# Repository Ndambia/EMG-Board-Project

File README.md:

# 3-Channel EMG Data Acquisition System (ESP32-Based)

## Overview

This project is a **3-channel Electromyography (EMG) Data Acquisition (DAQ) system** built around an **ESP32 MCU**. It is designed to acquire low-level biopotential signals from muscles, condition them using an analog front-end, digitize them via an external ADC, and transmit or store the data for further processing.

The system is modular and portable, integrating power management for battery operation, making it suitable for wearable and embedded biomedical applications.

---

## Key Features

* Three independent EMG input channels
* External multi-channel ADC with I²C interface
* ESP32 MCU for control, DSP, and communication
* Li-Po battery charging support
* Boost / regulation circuitry for stable operation
* Compact PCB designed for embedded and wearable use

---

## System Architecture

### Signal Chain Overview

```
Muscle Electrodes
      ↓
EMG Analog Front-End (DAQ)
      ↓
External ADC (3 Channels)
      ↓  I²C
ESP32 MCU
      ↓
USB / BLE / Wi-Fi 
```

---

## Functional Block Description

### 1. EMG DAQ (Analog Front-End)

* Three independent EMG channels
* Powered at **3.3 V**
* Outputs conditioned analog signals suitable for ADC input

**Typical functionality includes:**

* Instrumentation amplification
* High-pass filtering to remove motion artifacts
* Low-pass filtering to reduce high-frequency noise
* Optional 50/60 Hz notch filtering

---

### 2. Analog-to-Digital Converter (ADC)

* Powered at **3.3 V**
* Three analog input channels
* Digital interface: **I²C (SDA, SCL)**

The ADC digitizes the conditioned EMG signals for processing by the ESP32.

---

### 3. Microcontroller Unit (ESP32)

* Powered at **3.3 V**
* Configures and reads data from the ADC
* Performs optional digital signal processing (RMS, envelope extraction)
* Supports USB, BLE, and Wi-Fi communication

---

### 4. Power Management

#### Li-Po Battery Charger

* Supports single-cell Li-Po batteries
* USB-powered charging
* Enables portable operation

#### Boost / Regulation Circuit

* Maintains stable system voltage during battery discharge
* Ensures reliable operation of analog and digital blocks

---

## PCB Design

### PCB Back Layer

The back layer shows the ground plane distribution and return paths. Care was taken to maintain a low-impedance ground for the analog EMG front-end to minimize noise coupling from digital sections.

### PCB Front Layer

The front layer contains the majority of signal routing and component placement. Analog EMG paths are kept short and isolated from high-speed digital and power traces.

### PCB Routing Overview

This image provides an overall routing overview, highlighting trace organization, separation between analog and digital domains, and controlled routing for sensitive EMG signals.

### Routing – Front

The front routing layer illustrates how EMG signal traces are carefully routed with minimal vias to reduce interference and preserve signal integrity.

### Routing – Back

Back-side routing is primarily used for ground returns and power distribution, helping to maintain clean reference planes for low-noise acquisition.

### PCB 3D View

The 3D view shows overall board dimensions, component height clearance, and suitability for enclosure or wearable integration.

### PCB Front 3D View

This view highlights top-side component placement, including the ESP32 module, ADC, and EMG front-end circuitry.

### PCB Back 3D View

The back-side 3D view shows passive components, ground stitching vias, and mechanical layout considerations.

### Design Progress Snapshot

This image documents the PCB design progress during layout and routing stages.

### Schematics

The schematic captures the complete system design, including EMG analog front-end, ADC, ESP32 MCU, and power management circuitry.

---

## Intended Applications

* Multi-channel EMG signal acquisition
* Wearable biomedical research devices
* Prosthetics and rehabilitation research
* Gesture recognition and HMI systems
* Academic and laboratory EMG experimentation

---

## Design Notes & Safety

* Proper analog grounding and shielding are critical for low-noise EMG acquisition
* Use shielded electrode cables where possible
* This system is intended for **research and educational use only**
* Not certified for clinical or diagnostic applications

---

## Author

**Eng. Ndambia M.**
MyGen Solutions

---

## License & Disclaimer

This project is provided for **research and educational purposes only**. It is not a certified medical device and must not be used for clinical diagnosis or treatment.

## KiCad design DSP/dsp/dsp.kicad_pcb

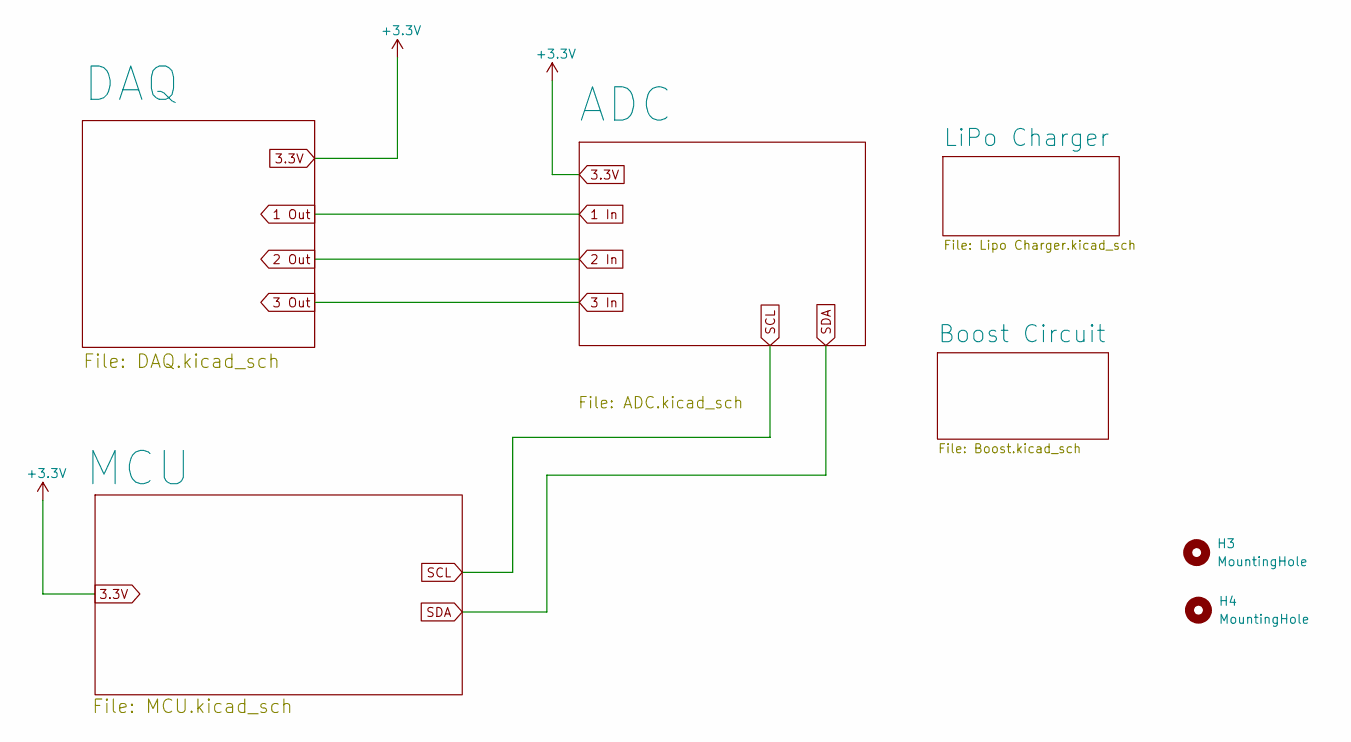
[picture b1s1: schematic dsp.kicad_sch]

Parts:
H3, H4: MountingHole; MountingHole_2.7mm_M2.5_Pad_Via

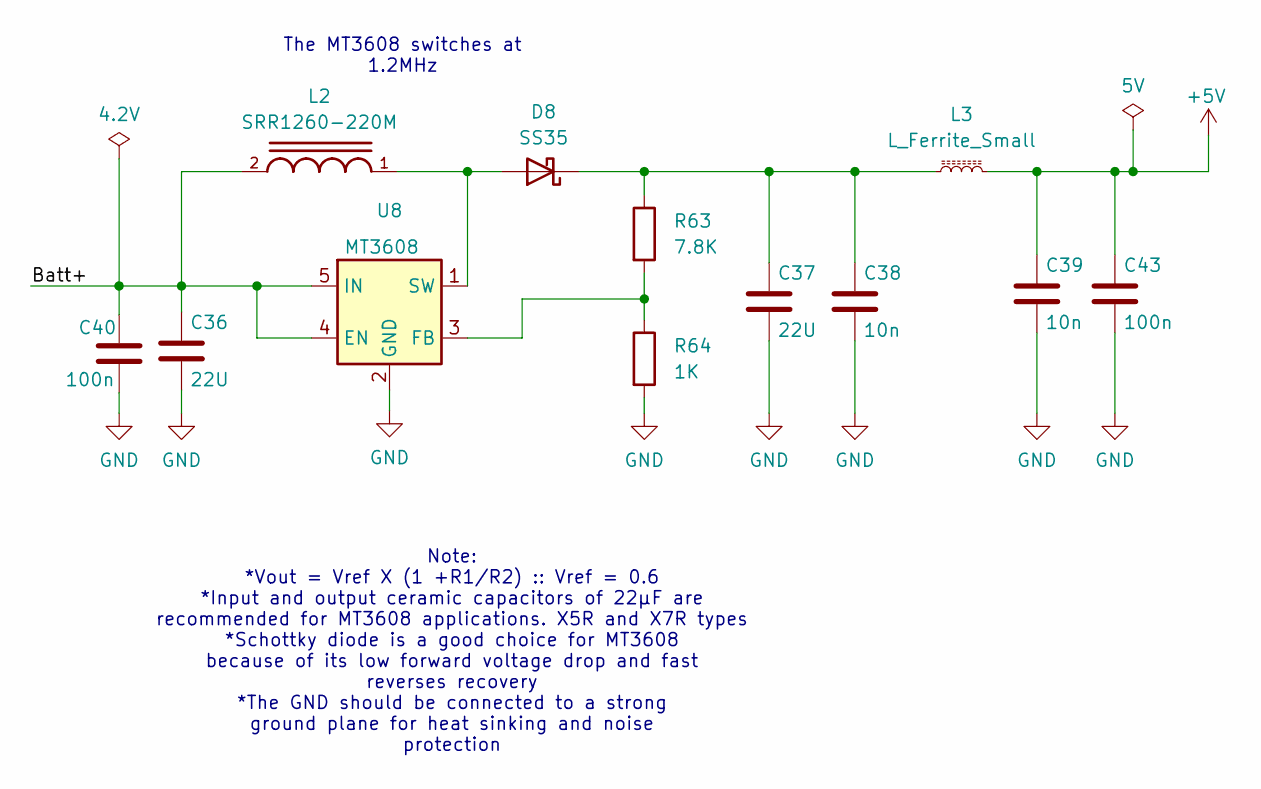
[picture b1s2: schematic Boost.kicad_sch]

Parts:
C36, C37: 22U; C_0201_0603Metric
C38, C39: 10n; C_0201_0603Metric
C40, C43: 100n; C_0201_0603Metric
D8: SS35; D_SMA
L2: SRR1260-220M; INDP125125X600N
L3: L_Ferrite_Small; L_0603_1608Metric
R63: 7.8K; R_0603_1608Metric
R64: 1K; R_0603_1608Metric
U8: MT3608; SOT-23-6

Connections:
5V: C39.1, C43.1, L3.2; also elsewhere on the board
/Boost Circuit/Batt+: C36.1, C40.1, L2.2, U8.4 (EN), U8.5 (IN)
GND: C36.2, C37.2, C38.2, C39.2, C40.2, C43.2, R64.2, U8.2 (GND); also elsewhere on the board
unnamed: D8.2 (A), L2.1, U8.1 (SW)
unnamed: C37.1, C38.1, D8.1 (K), L3.1, R63.1
unnamed: R63.2, R64.1, U8.3 (FB)

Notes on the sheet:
Note: *Vout = Vref X (1 +R1/R2) :: Vref = 0.6 *Input and output ceramic capacitors of 22μF are recommended for MT3608 applications. X5R and X7R types *Schottky diode is a good choice for MT3608 because of its low forward voltage drop and fast reverses recovery *The GND should be connected to a stro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
The MT3608 switches at 1.2MHz

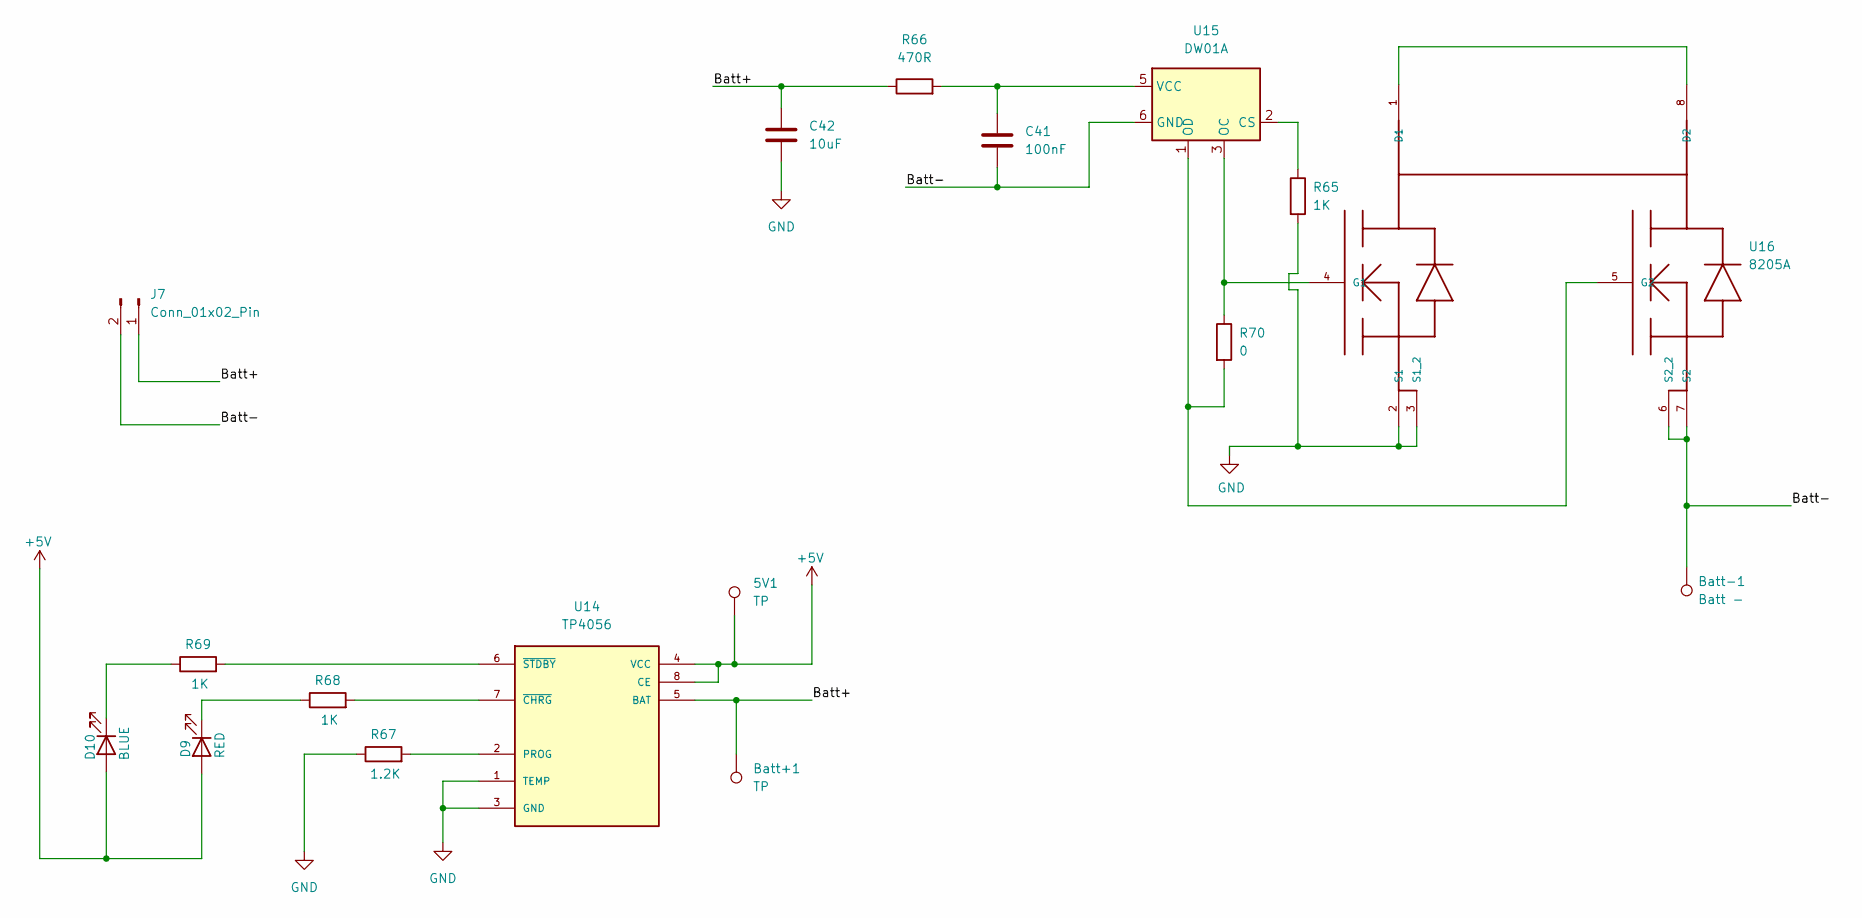
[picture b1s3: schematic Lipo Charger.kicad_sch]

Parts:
5V1: TP; TestPoint_Pad_D1.5mm
Batt+1: TP; TestPoint_Pad_D1.5mm
Batt-1: Batt -; TestPoint_Pad_D1.5mm
C41: 100nF; C_0201_0603Metric
C42: 10uF; C_0201_0603Metric
D9: RED; LED_0402_1005Metric
D10: BLUE; LED_0402_1005Metric
J7: Conn_01x02_Pin; JWT_A3963_1x02_P3.96mm_Vertical
R65, R68, R69: 1K; R_0603_1608Metric
R66: 470R; R_0603_1608Metric
R67: 1.2K; R_0603_1608Metric
R70: 0; R_0603_1608Metric
U14: TP4056; SOP127P600X175-9N
U15: DW01A; SOT-23-6
U16: 8205A; TSSOP8

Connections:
5V: 5V1.1, D9.2 (A), D10.2 (A), U14.4 (VCC), U14.8 (CE); also elsewhere on the board
/LiPo Charger/Batt+: Batt+1.1, C42.1, J7.1, R66.1, U14.5 (BAT)
/LiPo Charger/Batt-: Batt-1.1, C41.2, J7.2, U15.6 (GND), U16.6 (S2_2), U16.7 (S2)
GND: C42.2, R65.2, R67.1, U14.1 (TEMP), U14.3 (GND), U16.2 (S1), U16.3 (S1_2); also elsewhere on the board
unnamed: D9.1 (K), R68.1
unnamed: D10.1 (K), R69.1
unnamed: R67.2, U14.2 (PROG)
unnamed: R68.2, U14.7 (~CHRG)
unnamed: R69.2, U14.6 (~STDBY)
unnamed: R65.1, U15.2 (CS)
unnamed: R70.1, U15.3 (OC), U16.4 (G1)
unnamed: R70.2, U15.1 (OD), U16.5 (G2)
unnamed: C41.1, R66.2, U15.5 (VCC)
unnamed: U16.1 (D1), U16.8 (D2)

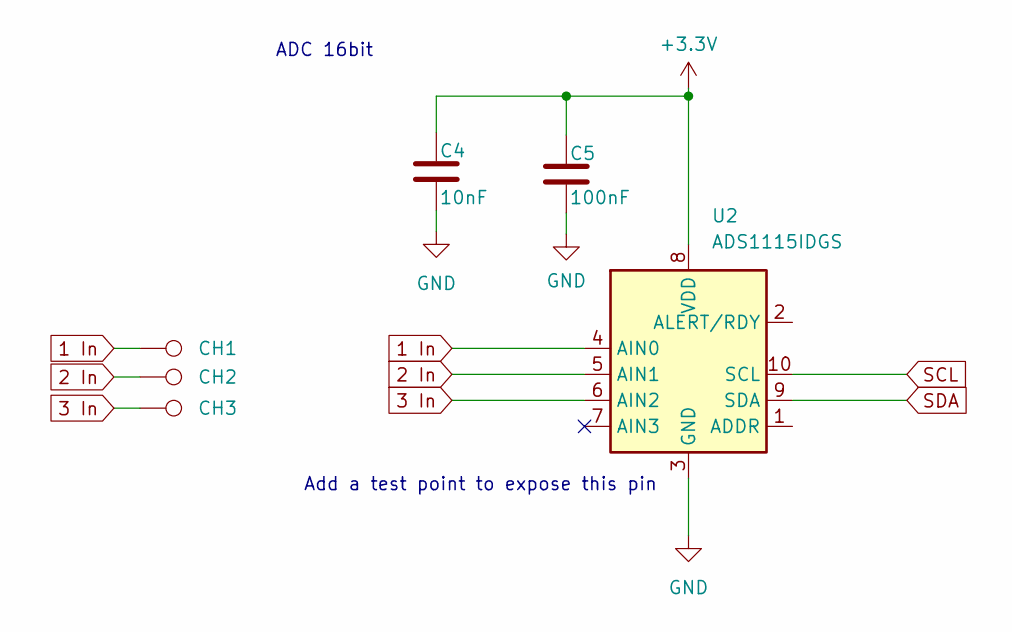
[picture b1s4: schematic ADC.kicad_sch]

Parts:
C4: 10nF; C_0603_1608Metric_Pad1.08x0.95mm_HandSolder
C5: 100nF; C_0603_1608Metric
CH1: 1; TestPoint_Pad_D1.0mm
CH2: 2; TestPoint_Pad_D1.0mm
CH3: 23; TestPoint_Pad_D1.0mm
U2: ADS1115IDGS; TSSOP-10_3x3mm_P0.5mm

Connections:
3.3V: C4.1, C5.1, U2.8 (VDD); also elsewhere on the board
GND: C4.2, C5.2, U2.3 (GND); also elsewhere on the board
SCL: U2.10 (SCL); also elsewhere on the board
SDA: U2.9 (SDA); also elsewhere on the board

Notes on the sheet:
ADC 16bit
Add a test point to expose this pin

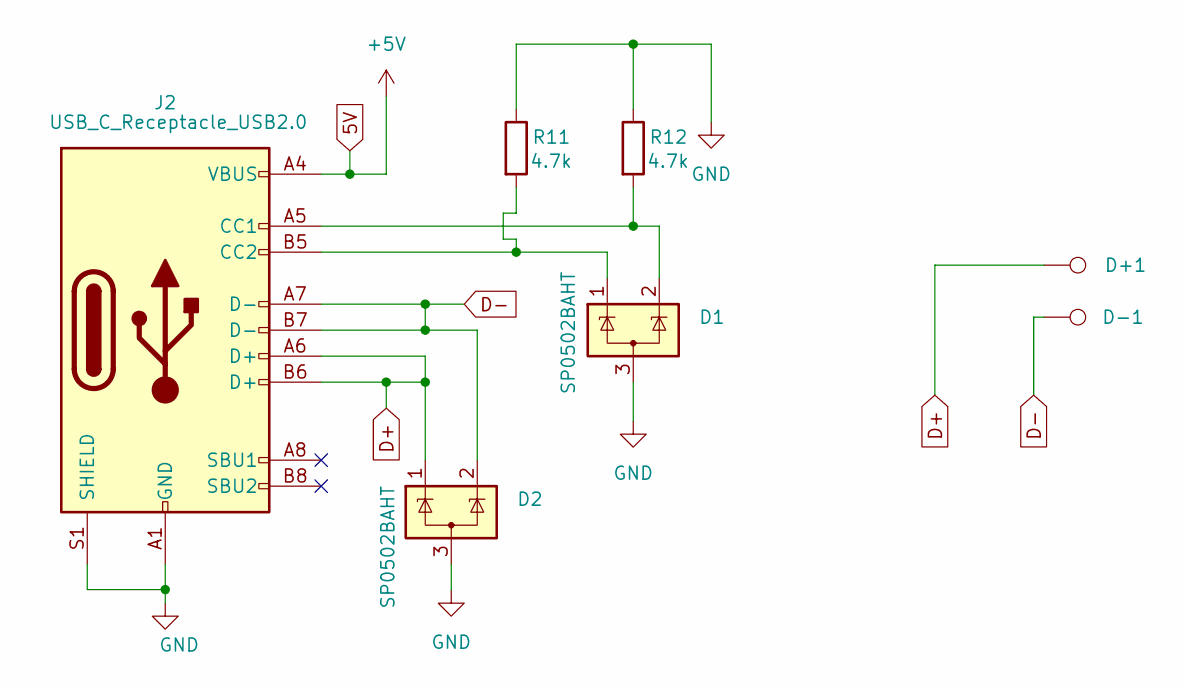
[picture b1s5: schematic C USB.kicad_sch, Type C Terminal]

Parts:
D1, D2: SP0502BAHT; SOT-23
D+1: D+; TestPoint_Pad_D1.0mm
D-1: D-; TestPoint_Pad_D1.0mm
J2: USB_C_Receptacle_USB2.0; USB_C_Receptacle_G-Switch_GT-USB-7010ASV
R11, R12: 4.7k; R_0201_0603Metric

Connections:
5V: J2.A4 (VBUS), J2.A9 (VBUS), J2.B4 (VBUS), J2.B9 (VBUS); also elsewhere on the board
D+: D2.1 (K), D+1.1, J2.A6 (D+), J2.B6 (D+); also elsewhere on the board
D-: D2.2 (K), D-1.1, J2.A7 (D-), J2.B7 (D-); also elsewhere on the board
GND: D1.3 (A), D2.3 (A), J2.A1 (GND), J2.A12 (GND), J2.B1 (GND), J2.B12 (GND), J2.S1 (SHIELD), R11.1, R12.1; also elsewhere on the board
unnamed: D1.2 (K), J2.A5 (CC1), R12.2
unnamed: D1.1 (K), J2.B5 (CC2), R11.2

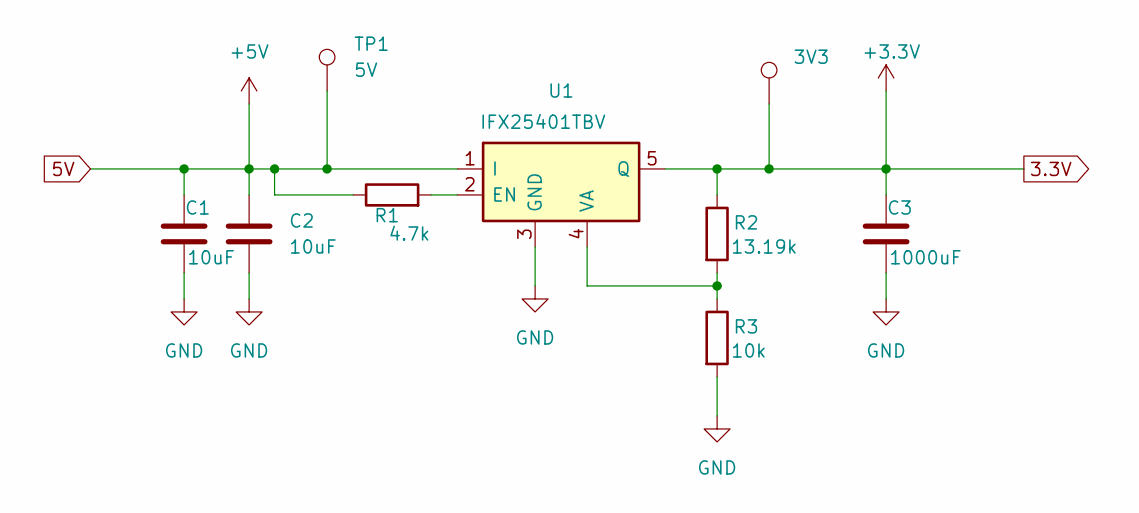
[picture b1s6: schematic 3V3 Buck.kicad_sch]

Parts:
3V3: TestPoint_Pad_D1.0mm
C1, C2: 10uF; C_0603_1608Metric_Pad1.08x0.95mm_HandSolder
C3: 1000uF; C_0603_1608Metric_Pad1.08x0.95mm_HandSolder
R1: 4.7k; R_0201_0603Metric
R2: 13.19k; R_0201_0603Metric
R3: 10k; R_0201_0603Metric
TP1: 5V; TestPoint_Pad_D1.0mm
U1: IFX25401TBV; TO-263-5_TabPin3

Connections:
3.3V: 3V3.1, C3.1, R2.1, U1.5 (Q); also elsewhere on the board
5V: C1.1, C2.1, R1.1, TP1.1, U1.1 (I); also elsewhere on the board
GND: C1.2, C2.2, C3.2, R3.2, U1.3 (GND); also elsewhere on the board
unnamed: R1.2, U1.2 (EN)
unnamed: R2.2, R3.1, U1.4 (VA)

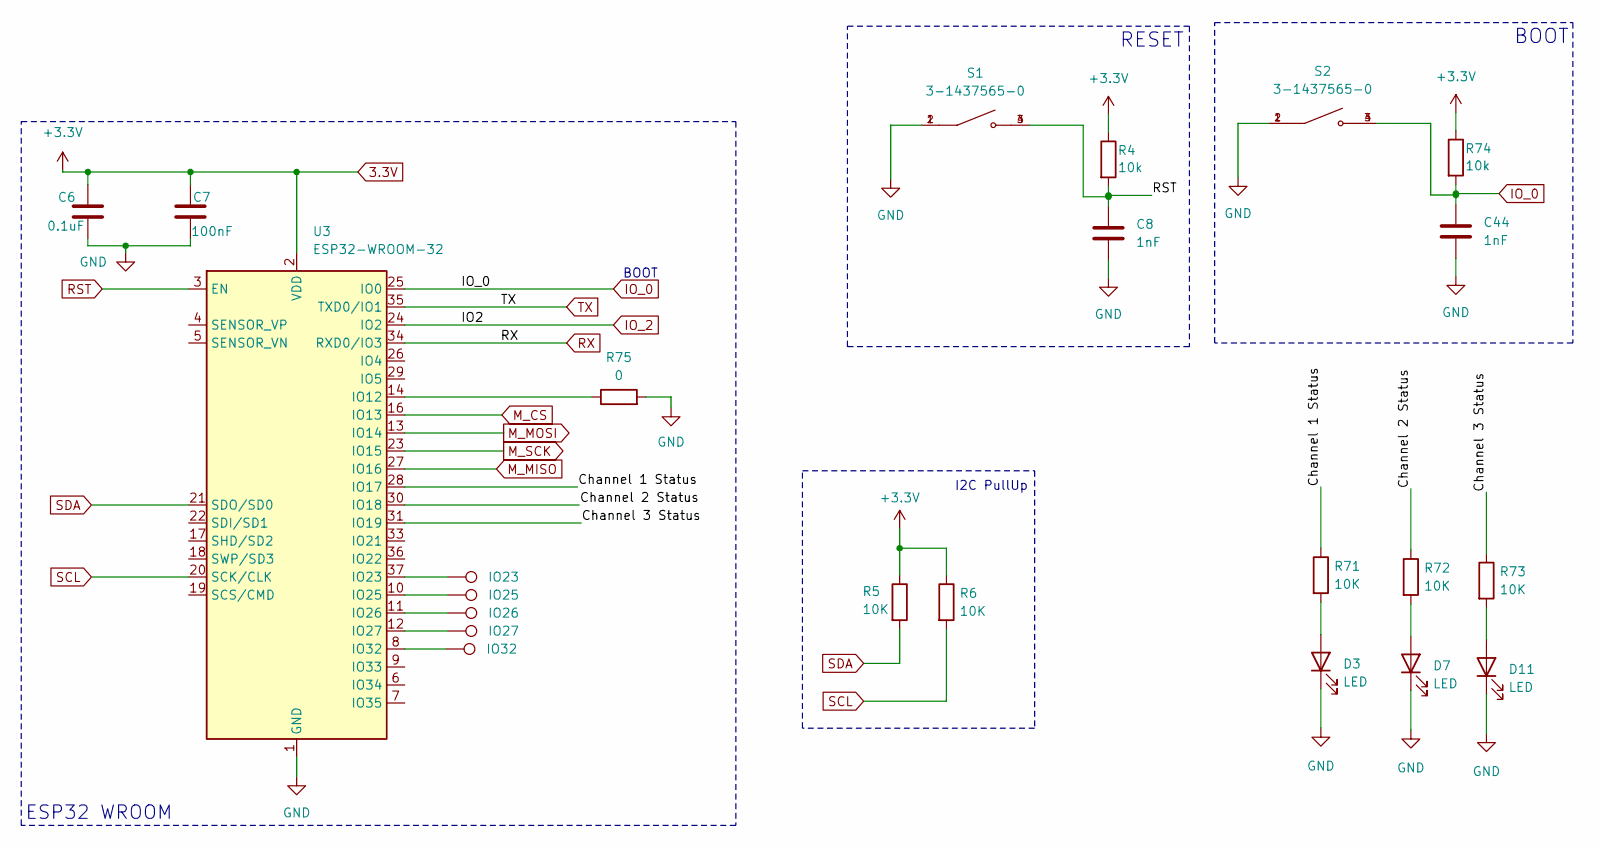
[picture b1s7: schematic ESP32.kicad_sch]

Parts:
C6: 0.1uF; C_0603_1608Metric
C7: 100nF; C_0603_1608Metric
C8, C44: 1nF; C_0402_1005Metric_Pad0.74x0.62mm_HandSolder
D3, D7, D11: LED; LED_0603_1608Metric_Pad1.05x0.95mm_HandSolder
IO23: 23; TestPoint_Pad_D1.0mm
IO25: 25; TestPoint_Pad_D1.0mm
IO26: 26; TestPoint_Pad_D1.0mm
IO27: 27; TestPoint_Pad_D1.0mm
IO32: 32; TestPoint_Pad_D1.0mm
R4, R74: 10k; R_0201_0603Metric
R5, R6, R71, R72, R73: 10K; R_0402_1005Metric
R75: 0; R_0402_1005Metric
S1, S2: 3-1437565-0; SW_3-1437565-0; PARTREV V
U3: ESP32-WROOM-32

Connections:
3.3V: C6.1, C7.1, R4.1, R5.1, R6.1, R74.1, U3.2 (VDD); also elsewhere on the board
/MCU/ESP32 Wroom/Channel 1 Status: R71.1, U3.28 (IO17)
/MCU/ESP32 Wroom/Channel 2 Status: R72.1, U3.30 (IO18)
/MCU/ESP32 Wroom/Channel 3 Status: R73.1, U3.31 (IO19)
GND: C6.2, C7.2, C8.2, C44.2, D3.1 (K), D7.1 (K), D11.1 (K), R75.2, S1.1, S1.2, S2.1, S2.2, U3.1 (GND), U3.15 (GND), U3.38 (GND), U3.39 (GND); also elsewhere on the board
IO_0: C44.1, R74.2, S2.3, S2.4, U3.25 (IO0); also elsewhere on the board
IO_2: U3.24 (IO2); also elsewhere on the board
M_CS: U3.16 (IO13); also elsewhere on the board
M_MISO: U3.27 (IO16); also elsewhere on the board
M_MOSI: U3.13 (IO14); also elsewhere on the board
M_SCK: U3.23 (IO15); also elsewhere on the board
unnamed: D3.2 (A), R71.2
unnamed: D7.2 (A), R72.2
unnamed: D11.2 (A), R73.2
unnamed: R75.1, U3.14 (IO12)
unnamed: IO23.1, U3.37 (IO23)
unnamed: IO25.1, U3.10 (IO25)
unnamed: IO26.1, U3.11 (IO26)
unnamed: IO27.1, U3.12 (IO27)
unnamed: IO32.1, U3.8 (IO32)
RST: C8.1, R4.2, S1.3, S1.4, U3.3 (EN); also elsewhere on the board
RX: U3.34 (RXD0/IO3); also elsewhere on the board
SCL: R6.2, U3.20 (SCK/CLK); also elsewhere on the board
SDA: R5.2, U3.21 (SDO/SD0); also elsewhere on the board
TX: U3.35 (TXD0/IO1); also elsewhere on the board

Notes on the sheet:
BOOT
RESET
ESP32 WROOM
BOOT
I2C PullUp

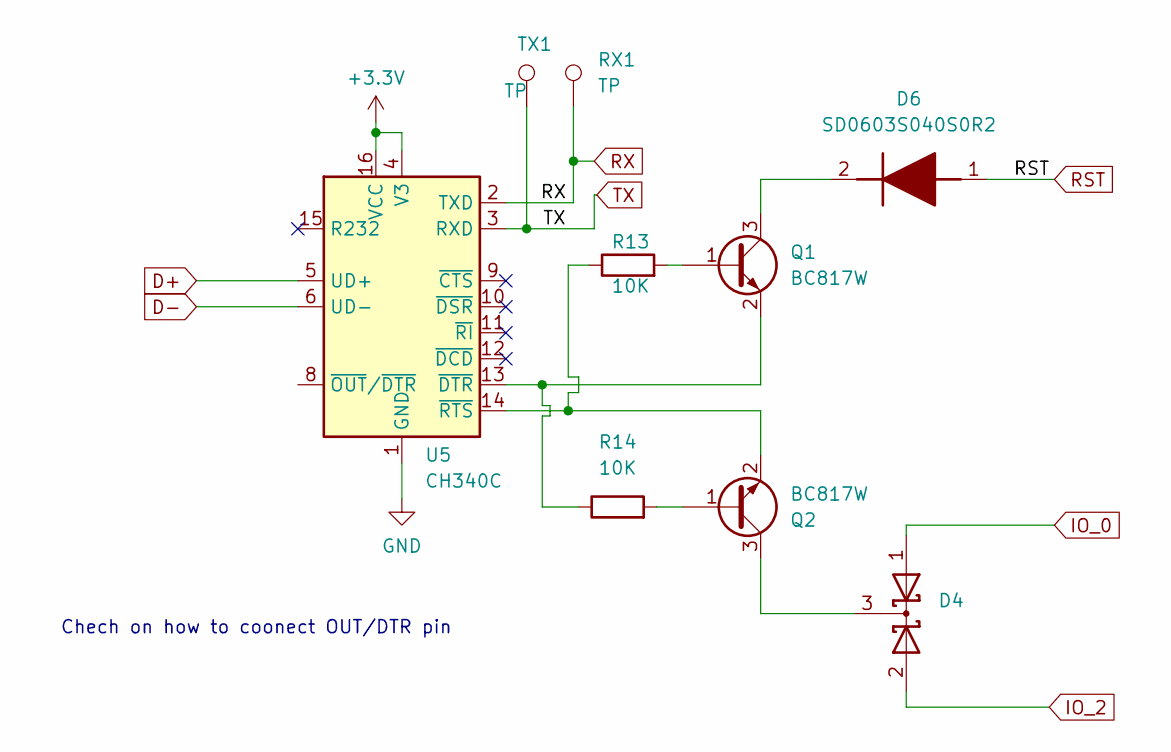
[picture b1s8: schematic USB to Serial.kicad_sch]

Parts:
D4: D_Schottky_Dual_CommonCathode_AAK; SOT95P230X110-3N
D6: SD0603S040S0R2; SD0603; Manufacturer_Part_Number SD0603S040S0R2; Mouser Part Number 581-SD0603S040S0R2
Q1, Q2: BC817W; SOT-323_SC-70
R13, R14: 10K; R_0402_1005Metric
RX1: TP; TestPoint_Pad_D1.5mm
TX1: TP; TestPoint_Pad_D1.5mm
U5: CH340C; SOIC-16_3.9x9.9mm_P1.27mm

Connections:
3.3V: U5.4 (V3), U5.16 (VCC); also elsewhere on the board
D+: U5.5 (UD+); also elsewhere on the board
D-: U5.6 (UD-); also elsewhere on the board
GND: U5.1 (GND); also elsewhere on the board
IO_0: D4.1 (A); also elsewhere on the board
IO_2: D4.2 (A); also elsewhere on the board
unnamed: D4.3 (K), Q2.3 (C)
unnamed: D6.2 (K), Q1.3 (C)
unnamed: Q1.1 (B), R13.2
unnamed: Q1.2 (E), R14.1, U5.13 (~DTR)
unnamed: Q2.1 (B), R14.2
unnamed: Q2.2 (E), R13.1, U5.14 (~RTS)
RST: D6.1 (A); also elsewhere on the board
RX: RX1.1, U5.2 (TXD); also elsewhere on the board
TX: TX1.1, U5.3 (RXD); also elsewhere on the board

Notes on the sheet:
Chech on how to coonect OUT/DTR pin

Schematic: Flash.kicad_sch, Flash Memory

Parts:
C9: 100nF; C_0603_1608Metric
U4: AT24CS64-SSHM; SOIC-8_3.9x4.9mm_P1.27mm

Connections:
3.3V: C9.2, U4.8 (VCC); also elsewhere on the board
GND: C9.1, U4.4 (GND); also elsewhere on the board
SCL: U4.6 (SCL); also elsewhere on the board
SDA: U4.5 (SDA); also elsewhere on the board

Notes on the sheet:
EEEPROM

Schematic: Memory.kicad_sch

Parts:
C10: 1u; C_0402_1005Metric
C11: 0.01u; C_0402_1005Metric
J1: MEM2052-00-195-00-A_REVA; GCT_MEM2052-00-195-00-A_REVA; PARTREV A
R7, R8, R9, R10: 10k; R_0402_1005Metric

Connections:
3.3V: C10.1, C11.1, J1.P4 (VDD), R7.1, R8.1, R9.1, R10.1; also elsewhere on the board
GND: C10.2, C11.2, J1.G1 (SHIELD_GND), J1.G2 (SHIELD_GND), J1.G3 (SHIELD_GND), J1.G4 (SHIELD_GND), J1.P6 (VSS); also elsewhere on the board
M_CS: J1.P2 (CD/DAT3), R8.2; also elsewhere on the board
M_MISO: J1.P7 (DAT0), R7.2; also elsewhere on the board
M_MOSI: J1.P3 (CMD), R10.2; also elsewhere on the board
M_SCK: J1.P5 (CLK), R9.2; also elsewhere on the board

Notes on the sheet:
SPI PULLUP RESISTORS

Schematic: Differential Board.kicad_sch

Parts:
C16, C17, C19, C25, C31: 0.1uF; C_0201_0603Metric
C18, C21, C23, C24, C27, C29, C30, C33, C35: 10nF; C_0201_0603Metric
C20, C26, C32: 240nF; C_0201_0603Metric
C22, C28, C34: 120nF; C_0201_0603Metric
ELEC1+1, ELEC1-1, ELEC2+1, ELEC2-1, ELEC3+1, ELEC3-1: 2; TestPoint_Pad_D1.0mm
FGND1: 2; TestPoint_Pad_D1.0mm
FIL1, FIL2, FIL3: 2; TestPoint_Pad_D1.0mm
J4, J5, J6: Conn_01x03_Pin; PinHeader_1x03_P1.27mm_Vertical_SMD_Pin1Left
R21, R22, R26, R27, R31, R33, R34, R35, R36, R40, R41, R45, R47, R48, R49, R50, R54, R55, R57, R59, R61, R62: 10k; R_0603_1608Metric_Pad0.98x0.95mm_HandSolder
R23, R37, R51: 2.2K; R_0603_1608Metric_Pad0.98x0.95mm_HandSolder
R24, R38, R52: 2.2k; R_0603_1608Metric_Pad0.98x0.95mm_HandSolder
R25, R28, R29, R30, R39, R42, R43, R44, R53, R56, R58: 1k; R_0603_1608Metric_Pad0.98x0.95mm_HandSolder
R32, R46, R60: 470; R_0402_1005Metric
RAW1, RAW2, RAW3: 1; TestPoint_Pad_D1.0mm
REF_GND1: 2; TestPoint_Pad_D1.0mm
U7, U9, U11: LM324A; SOIC127P600X175-14N
U10, U12, U13: INA125P; DIP794W45P254L1969H508Q16

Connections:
3.3V: R22.2, R36.2, R50.2; also elsewhere on the board
12V: C16.1, C17.1, C18.1, C19.1, C24.1, C25.1, C30.1, C31.1, R21.1, R35.1, R49.1, U7.4 (V+), U9.4 (V+), U10.1 (V+), U11.4 (V+), U12.1 (V+), U13.1 (V+); also elsewhere on the board
+ Electrode: ELEC1+1.1, J5.2, R33.1, U10.6 (V+IN)
+ Electrode 2: ELEC2-1.1, J4.2, R47.1, U12.6 (V+IN)
+ Electrode 3: ELEC3+1.1, J6.2, R61.1, U13.6 (V+IN)
- Electrode: ELEC1-1.1, J5.3, R34.1, U10.7 (V-IN)
- Electrode 2: ELEC2+1.1, J4.3, R48.1, U12.7 (V-IN)
- Electrode 3: ELEC3-1.1, J6.3, R62.1, U13.7 (V-IN)
Float GND: FGND1.1, J4.1, J5.1, J6.1, R33.2, R34.2, R47.2, R48.2, R61.2, R62.2, REF_GND1.1, U10.12 (VREFCOM), U12.12 (VREFCOM), U13.12 (VREFCOM); also elsewhere on the board
Float GND 2: C22.2, C23.1, C28.2, C29.2, C34.2, C35.2, R28.1, R30.1, R42.1, R44.1, R56.1, R58.1, U10.4 (VREFOUT), U10.5 (IAREF), U10.13 (VREFBG), U12.4 (VREFOUT), U12.5 (IAREF), U12.13 (VREFBG), U13.4 (VREFOUT), U13.5 (IAREF), U13.13 (VREFBG); also elsewhere on the board
GND: C16.2, C17.2, C18.2, C19.2, C24.2, C25.2, C30.2, C31.2, R26.1, R40.1, R54.1, U7.11 (V-), U9.11 (V-), U10.3 (V-), U11.11 (V-), U12.3 (V-), U13.3 (V-); also elsewhere on the board
unnamed: C20.1, R23.2, R24.1
unnamed: C21.1, R29.2, U9.8
unnamed: C23.2, R27.2
unnamed: C26.1, R37.2, R38.1
unnamed: C27.1, R43.2, U11.8
unnamed: C29.1, R41.2
unnamed: C32.1, R51.2, R52.1
unnamed: C33.1, R59.2, U7.14
unnamed: C35.1, R55.2
unnamed: R23.1, R25.2, U9.1
unnamed: R32.1, U10.8 (RG)
unnamed: R32.2, U10.9 (RG)
unnamed: R37.1, R39.2, U11.1
unnamed: R46.1, U12.8 (RG)
unnamed: R46.2, U12.9 (RG)
unnamed: R51.1, R53.2, U7.7
unnamed: R60.1, U13.8 (RG)
unnamed: R60.2, U13.9 (RG)
unnamed: R53.1, R55.1, U7.6 (-)
unnamed: C34.1, R52.2, U7.10 (+)
unnamed: R56.2, R57.1, U7.9 (-)
unnamed: C32.2, FIL3.1, R57.2, U7.8, U7.12 (+)
unnamed: R58.2, R59.1, U7.13 (-)
unnamed: R25.1, R27.1, U9.2 (-)
unnamed: C22.1, R24.2, U9.5 (+)
unnamed: R30.2, R31.1, U9.6 (-)
unnamed: C20.2, FIL1.1, R31.2, U9.7, U9.10 (+)
unnamed: R28.2, R29.1, U9.9 (-)
unnamed: RAW1.1, U9.3 (+), U10.10 (VO), U10.11 (SENSE)
unnamed: R21.2, U10.2 (~SLEEP)
unnamed: RAW2.1, U11.3 (+), U12.10 (VO), U12.11 (SENSE)
unnamed: R39.1, R41.1, U11.2 (-)
unnamed: C28.1, R38.2, U11.5 (+)
unnamed: R44.2, R45.1, U11.6 (-)
unnamed: C26.2, FIL2.1, R45.2, U11.7, U11.10 (+)
unnamed: R42.2, R43.1, U11.9 (-)
unnamed: R35.2, U12.2 (~SLEEP)
unnamed: RAW3.1, U7.5 (+), U13.10 (VO), U13.11 (SENSE)
unnamed: R49.2, U13.2 (~SLEEP)

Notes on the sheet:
Channel Two
Channel Three
Channel One

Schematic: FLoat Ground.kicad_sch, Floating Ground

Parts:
C14, C15: 100uF; CP_Elec_3x5.4
R17, R18, R19, R20: 10k; R_0603_1608Metric_Pad0.98x0.95mm_HandSolder
U7: LM324A; SOIC127P600X175-14N

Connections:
12V: C14.1, R17.1, R18.1; also elsewhere on the board
Float GND: C14.2, C15.1, R18.2, R19.1; also elsewhere on the board
Float GND 2: U7.1, U7.2 (-); also elsewhere on the board
GND: C15.2, R19.2, R20.2; also elsewhere on the board
unnamed: R17.2, R20.1, U7.3 (+)

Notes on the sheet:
V Clamp and Floating Ground

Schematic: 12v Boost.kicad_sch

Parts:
C12: 1u; C_0402_1005Metric
C13: 1u; C_0603_1608Metric
D5: 1N5819; D_SOD-123
L1: 10uH; L_Cenker_CKCS3012; MPN FXL0420-100-M
R15: 48.7K; R_0402_1005Metric
R16: 5.6K; R_0402_1005Metric
U6: AP3012; SOT-23-5

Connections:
3.3V: C12.1, L1.1, U6.4 (~SHDN), U6.5 (IN); also elsewhere on the board
12V: C13.1, D5.1 (K), R15.1; also elsewhere on the board
GND: C12.2, C13.2, R16.2, U6.2 (GND); also elsewhere on the board
unnamed: D5.2 (A), L1.2, U6.1 (SW)
unnamed: R15.2, R16.1, U6.3 (FB)

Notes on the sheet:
3V3 to 12V

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
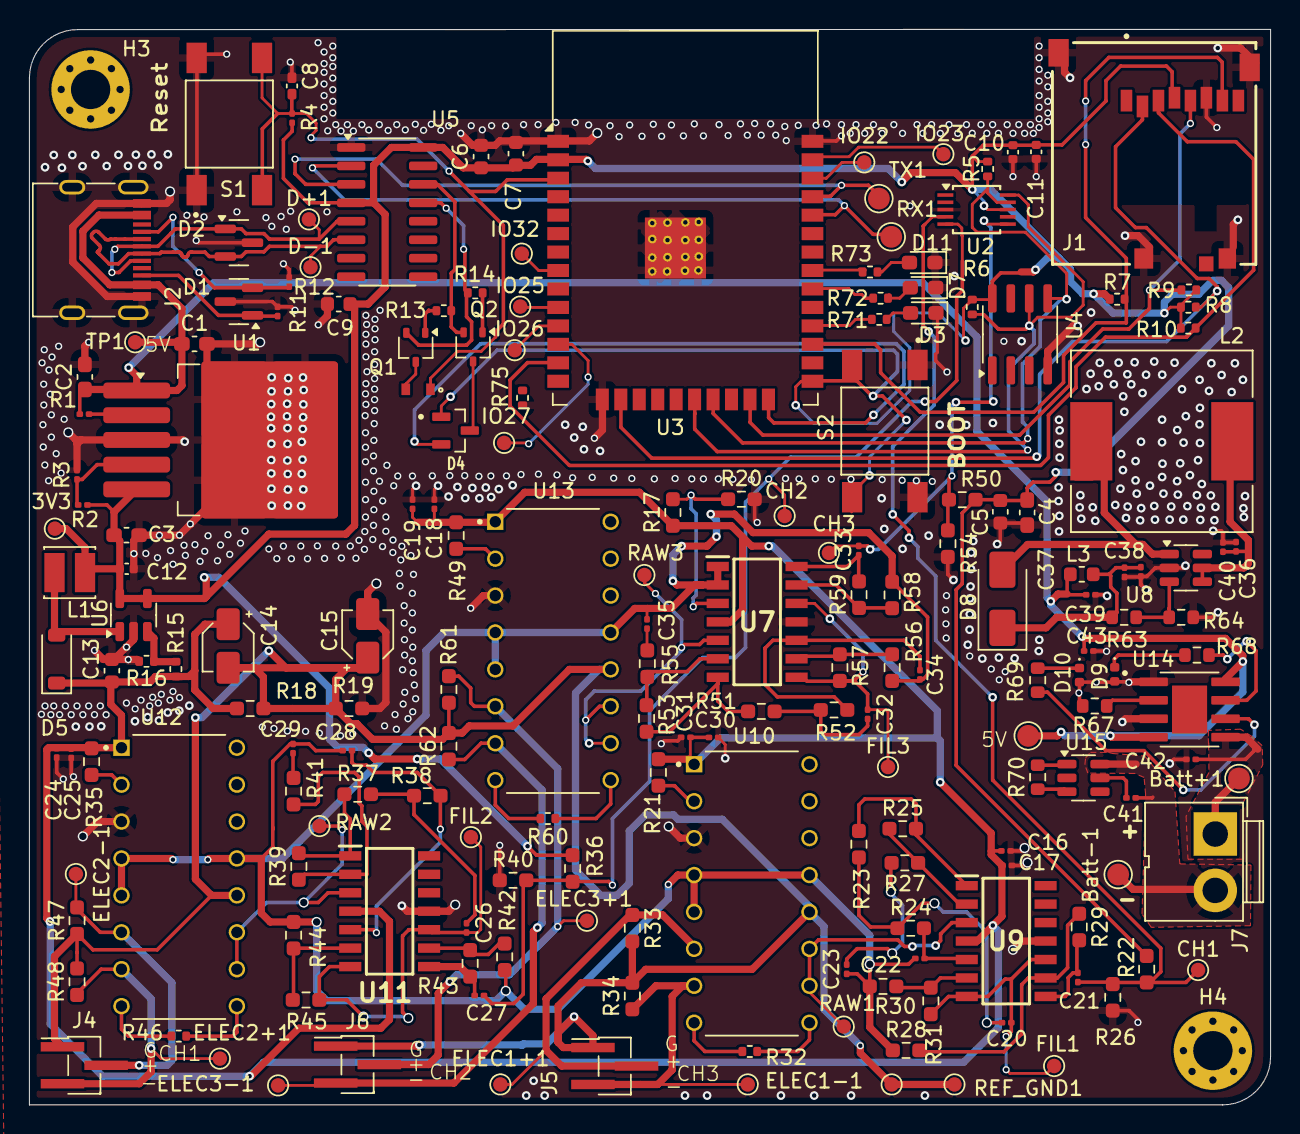
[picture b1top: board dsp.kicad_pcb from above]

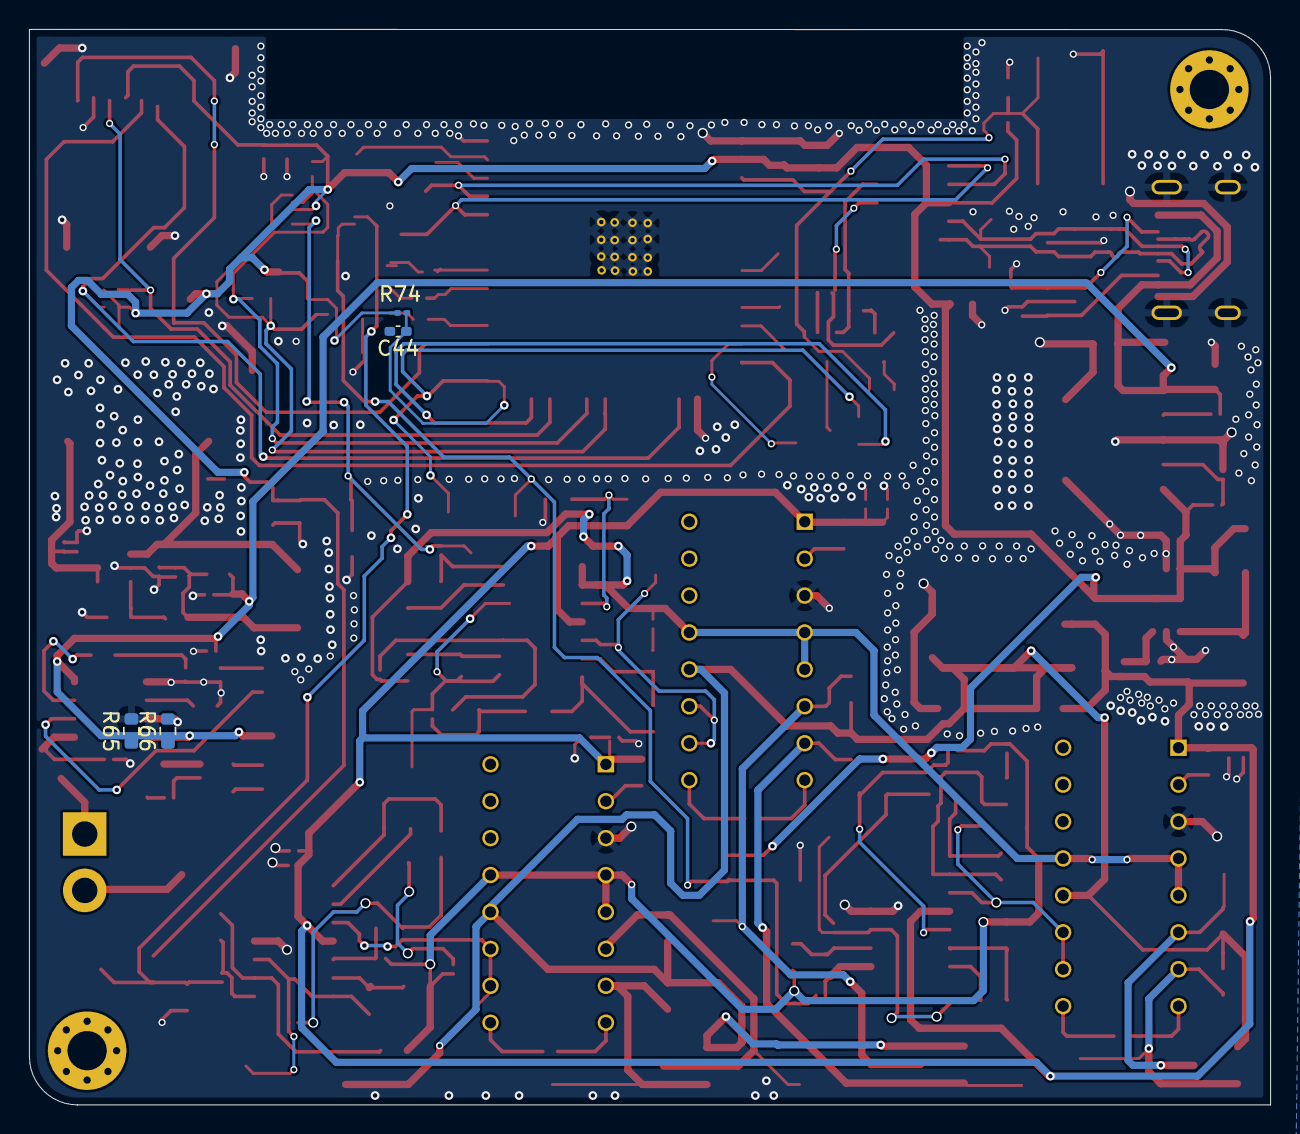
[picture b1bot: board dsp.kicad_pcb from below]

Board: 2 copper layers, 85.4 x 74.0 mm, 192 parts (4 on the bottom side), 107 nets.

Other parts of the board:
IO22: 22; TestPoint_Pad_D1.0mm

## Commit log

2026-02-03 Add README for 3-Channel EMG Data Acquisition System
    Added detailed documentation for a 3-channel EMG data acquisition system, including overview, features, system architecture, functional block descriptions, PCB design, intended applications, design n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
2026-03-31 Update communication options in README
    Removed 'Data Storage' from the communication options.
